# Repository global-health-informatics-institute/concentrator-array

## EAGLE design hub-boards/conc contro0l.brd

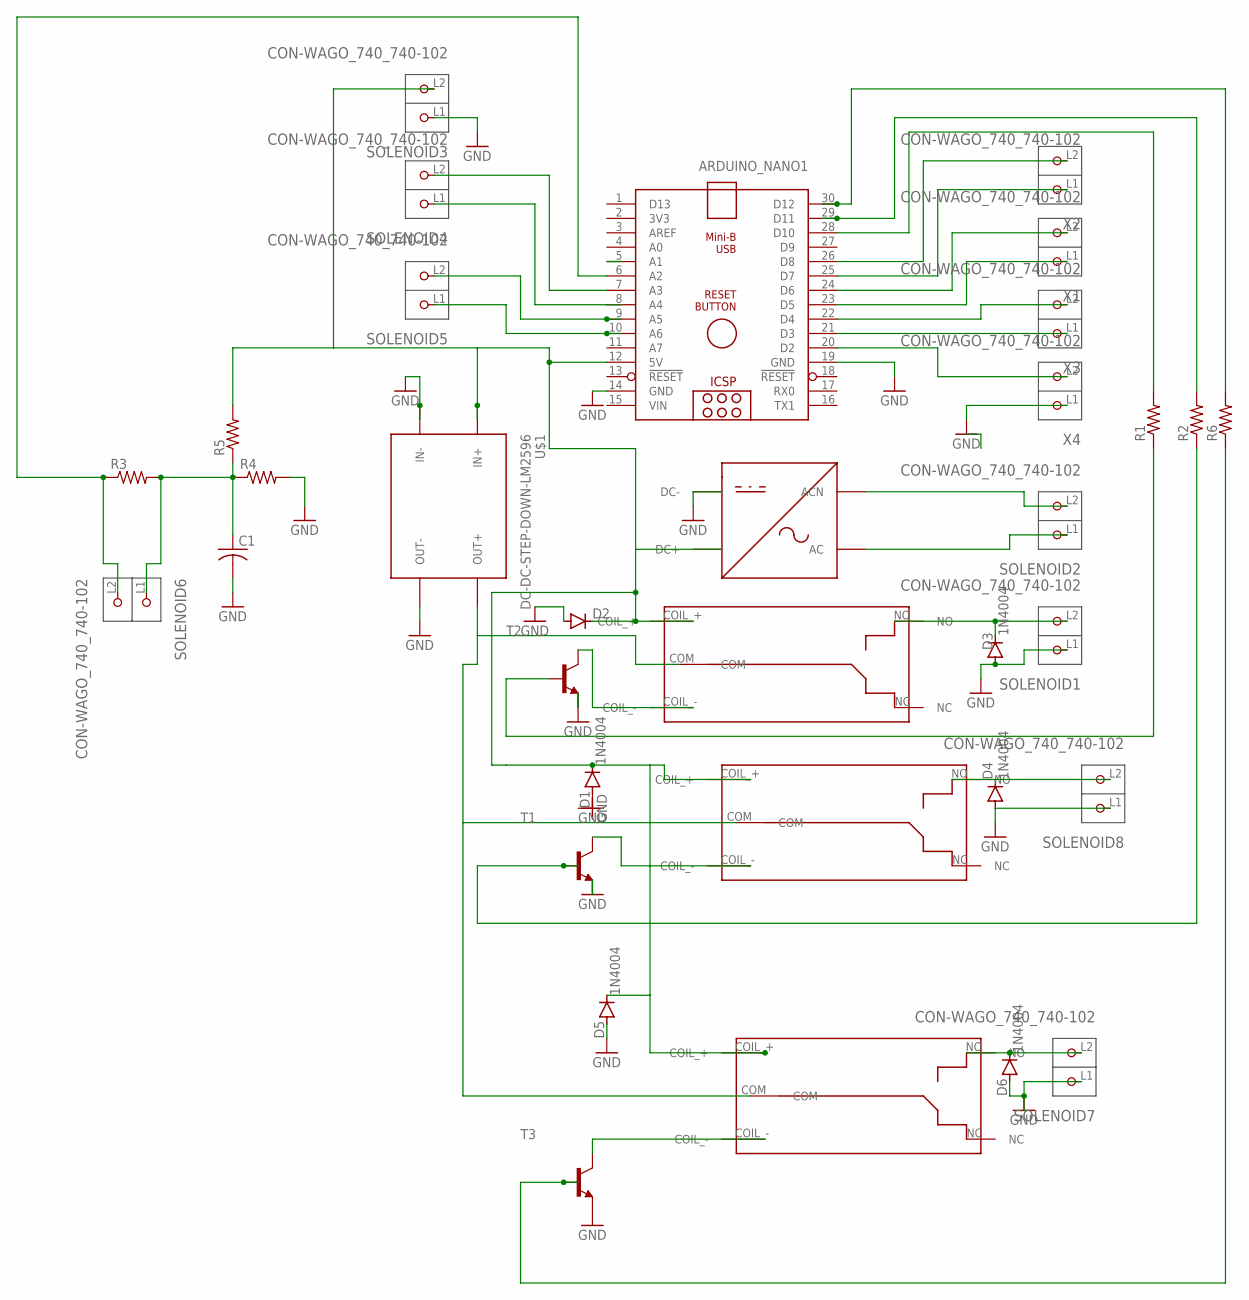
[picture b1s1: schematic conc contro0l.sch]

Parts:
ACDC: RPD10W1S; 2343
ARDUINO_NANO1: ARDUINONANOV30-GHIT_ARDUINO_NANO
C1: C-US025-024X044; C025-024X044
D1, D2, D3, D4, D5, D6: 1N4004; DO41-10
R1, R2, R6: R-US_0411/15; 0411/15
R3, R4, R5: R-US_0309/10; 0309/10
SOLENOID1, SOLENOID2, SOLENOID3, SOLENOID4, SOLENOID5, SOLENOID6, SOLENOID7, SOLENOID8: CON-WAGO_740_740-102; CON-WAGO_740_P-740-102
T1, T2, T3: 2N2222-NPN-TO92-EBC; TO92-EBC
U$1: DC-DC-STEP-DOWN-LM2596
U$2, U$3, U$4: RELAY_JQC-3F(T73)A; JQC-3F(T73)
X1, X2, X3, X4: CON-WAGO_740_740-102; CON-WAGO_740_P-740-102

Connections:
GND: ACDC.DC-, ARDUINO_NANO1.14 (GND), ARDUINO_NANO1.19 (GND), C1.2, D1.A, D2.A, D3.A, D4.A, D5.A, D6.A, R4.2, SOLENOID1.L1 (P1), SOLENOID3.L1 (P1), SOLENOID7.L1 (P1), SOLENOID8.L1 (P1), T1.E, T2.E, T3.E, U$1.IN-, U$1.OUT-, X4.L1 (P1)
unnamed: ARDUINO_NANO1.7 (A3), SOLENOID4.L2 (P2)
unnamed: ARDUINO_NANO1.20 (D2), X4.L2 (P2)
unnamed: ARDUINO_NANO1.21 (D3), X3.L1 (P1)
unnamed: ARDUINO_NANO1.22 (D4), X3.L2 (P2)
unnamed: ARDUINO_NANO1.23 (D5), X1.L1 (P1)
unnamed: ARDUINO_NANO1.24 (D6), X1.L2 (P2)
unnamed: ARDUINO_NANO1.28 (D10), R1.2
unnamed: ARDUINO_NANO1.26 (D8), X2.L2 (P2)
unnamed: ARDUINO_NANO1.9 (A5), SOLENOID5.L2 (P2)
unnamed: ACDC.DC+, ARDUINO_NANO1.12 (5V), D1.C, D2.C, D5.C, R5.2, SOLENOID3.L2 (P2), U$1.IN+, U$2.COIL_+, U$3.COIL_+, U$4.COIL_+
unnamed: ACDC.ACN, SOLENOID2.L2 (P2)
unnamed: ARDUINO_NANO1.10 (A6), SOLENOID5.L1 (P1)
unnamed: D3.C, SOLENOID1.L2 (P2), U$2.NO
unnamed: D4.C, SOLENOID8.L2 (P2), U$3.NO
unnamed: T2.C, U$2.COIL_-
unnamed: R2.1, T1.B
unnamed: ARDUINO_NANO1.25 (D7), X2.L1 (P1)
unnamed: ACDC.AC, SOLENOID2.L1 (P1)
unnamed: C1.1, R3.2, R4.1, R5.1, SOLENOID6.L1 (P1)
unnamed: R1.1, T2.B
unnamed: T1.C, U$3.COIL_-
unnamed: ARDUINO_NANO1.8 (A4), SOLENOID4.L1 (P1)
unnamed: R6.1, T3.B
unnamed: ARDUINO_NANO1.6 (A2), R3.1, SOLENOID6.L2 (P2)
unnamed: U$1.OUT+, U$2.COM, U$3.COM, U$4.COM
unnamed: ARDUINO_NANO1.29 (D11), R2.2
unnamed: ARDUINO_NANO1.30 (D12), R6.2
unnamed: T3.C, U$4.COIL_-
unnamed: D6.C, SOLENOID7.L2 (P2), U$4.NO
VIN: ARDUINO_NANO1.15 (VIN)

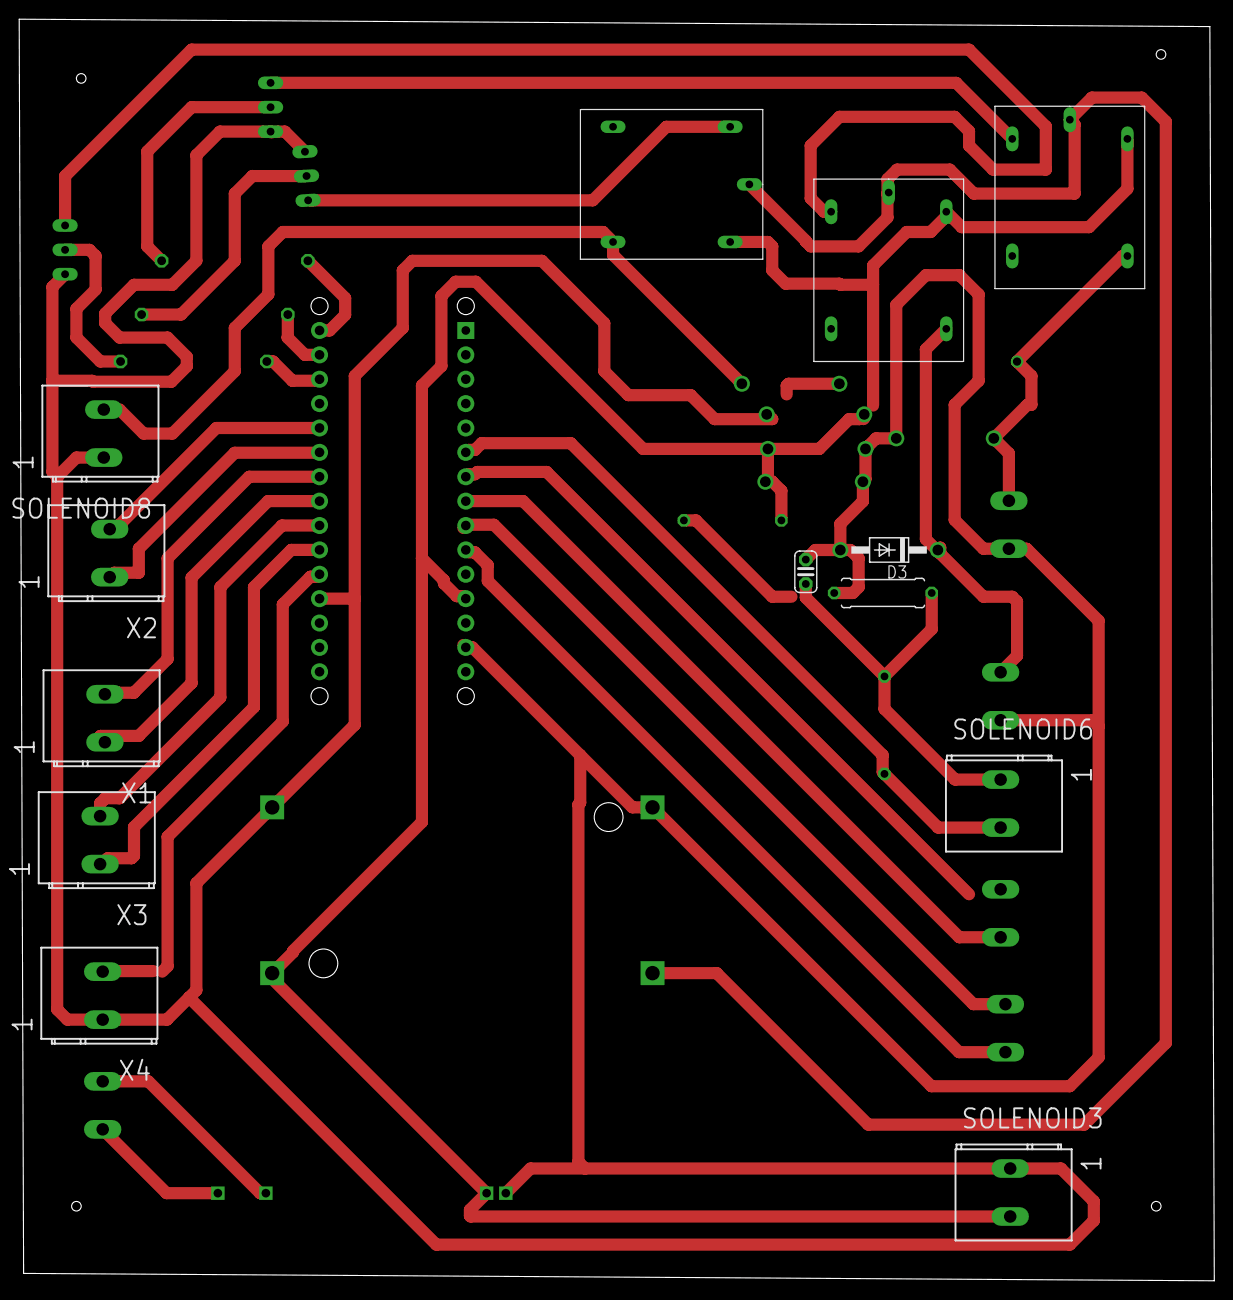
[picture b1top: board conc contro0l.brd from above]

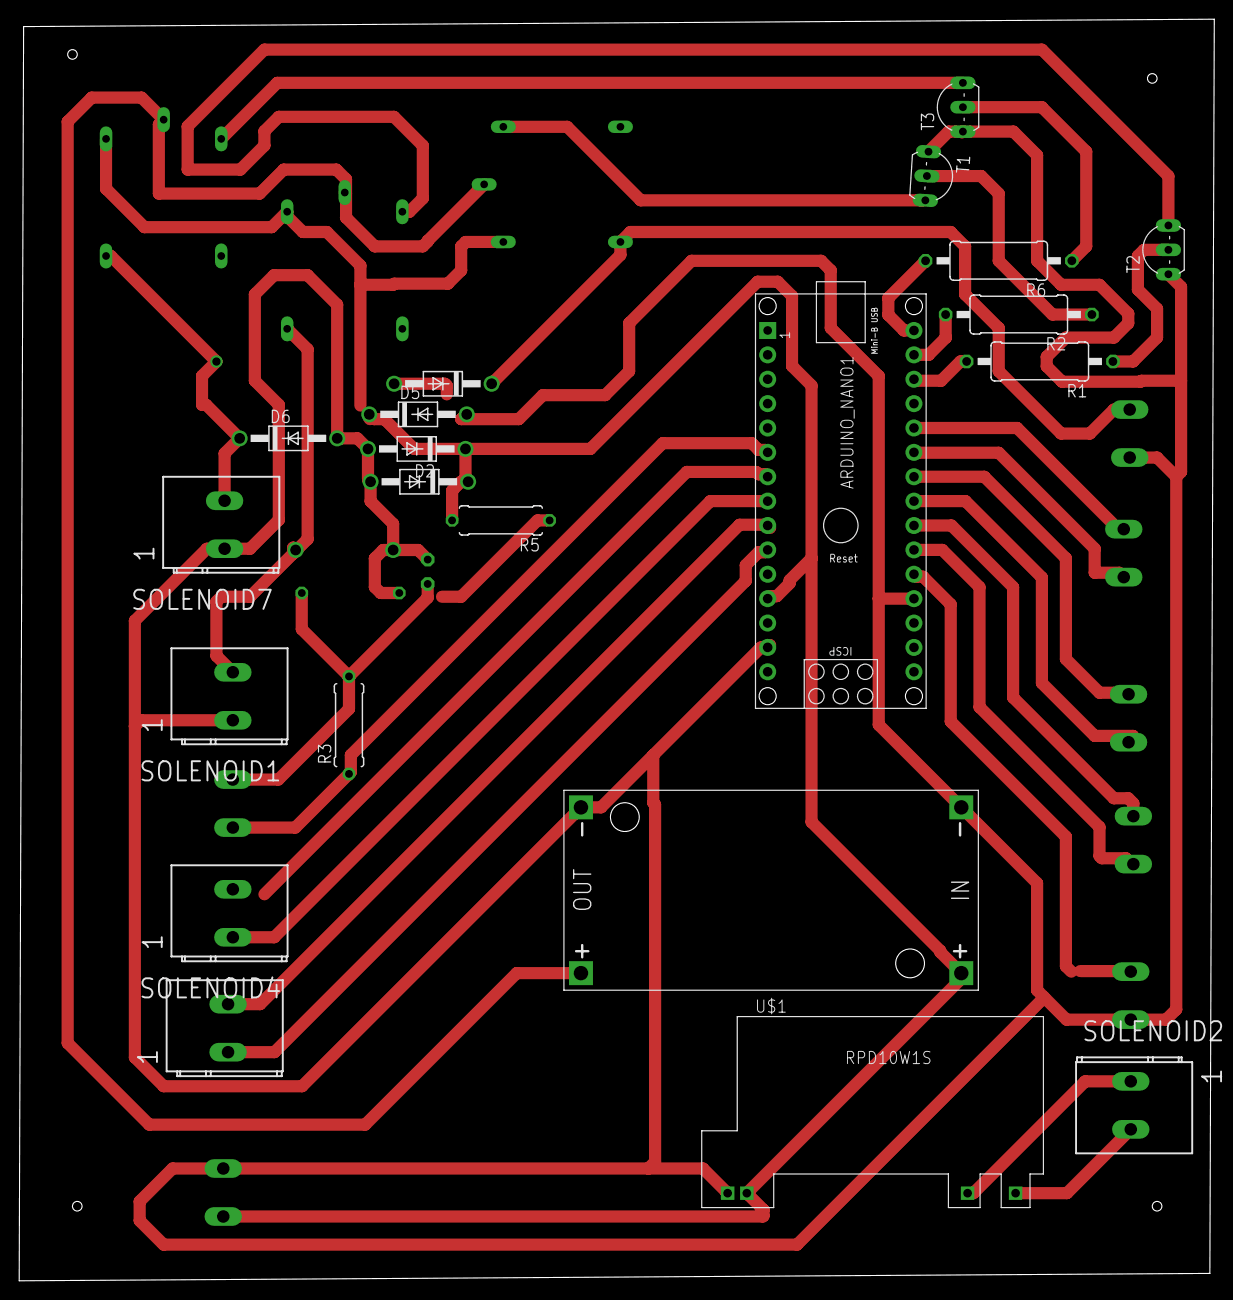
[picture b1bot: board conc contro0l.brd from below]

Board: 2 copper layers, 124.5 x 131.4 mm, 34 parts (21 on the bottom side), 30 nets.

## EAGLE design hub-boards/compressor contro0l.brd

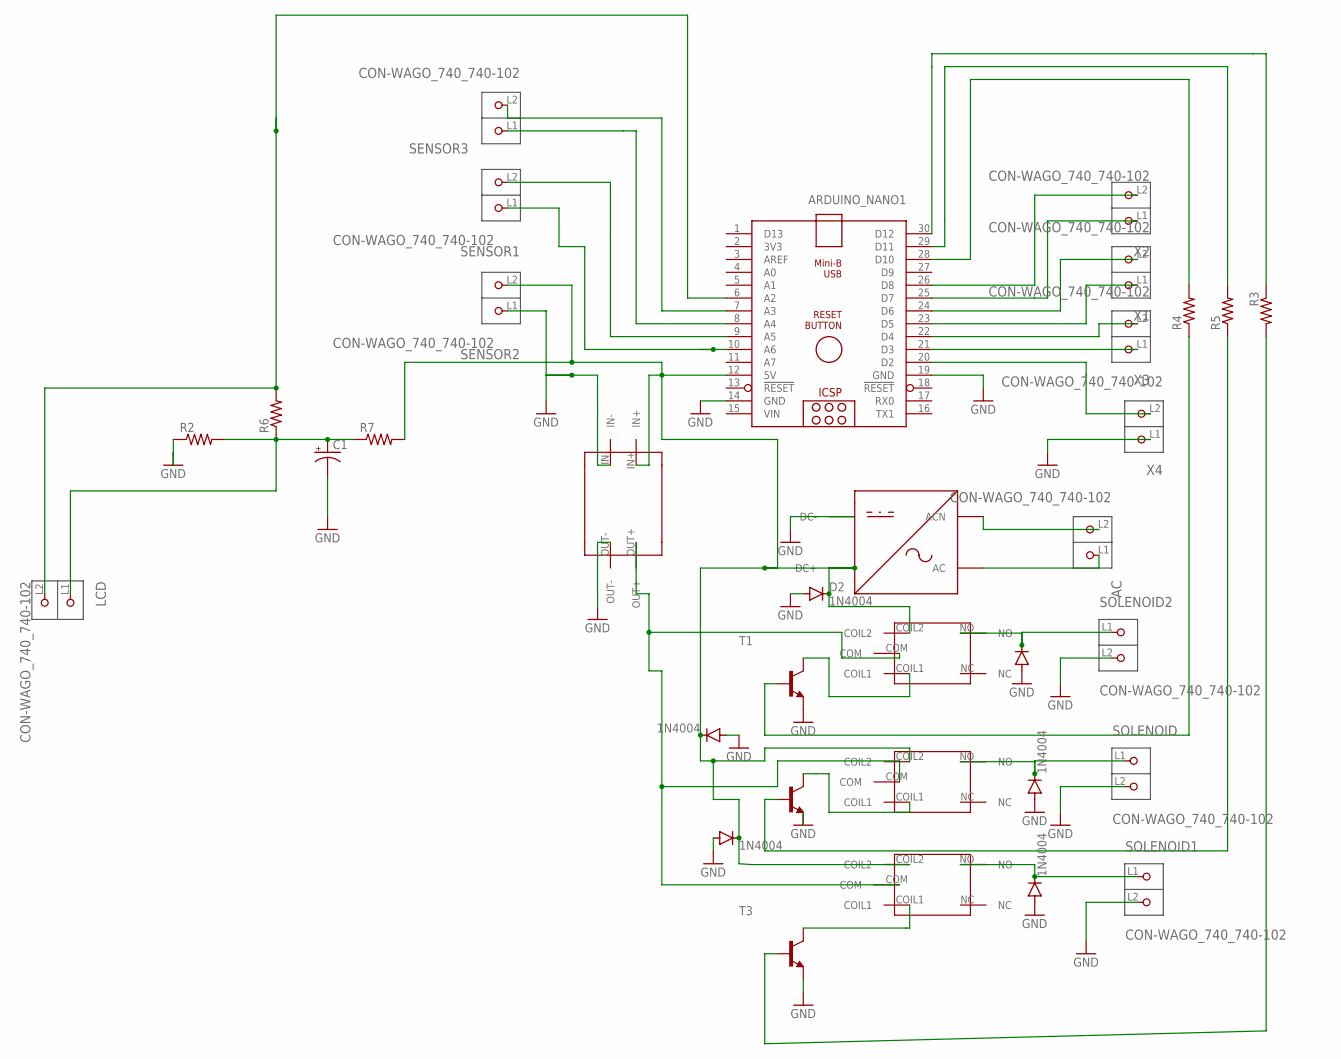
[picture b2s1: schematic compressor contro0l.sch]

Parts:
AC: CON-WAGO_740_740-102; CON-WAGO_740_P-740-102
ACDC: RPD10W1S; 2343
ARDUINO_NANO1: ARDUINONANOV30-GHIT_ARDUINO_NANO
C1: CPOL-USE3.5-8; E3,5-8
D2, D3, D4, D5, D6, D7: 1N4004; DO41-10
LCD: CON-WAGO_740_740-102; CON-WAGO_740_P-740-102
R2, R6, R7: R-US_0207/10; 0207/10
R3, R4, R5: R-US_0613/15; P0613/15
SENSOR1, SENSOR2, SENSOR3: CON-WAGO_740_740-102; CON-WAGO_740_P-740-102
SOLENOID, SOLENOID1, SOLENOID2: CON-WAGO_740_740-102; CON-WAGO_740_P-740-102
T1, T2, T3: 2N2222-NPN-TO92-EBC; TO92-EBC
U$2: DC-DCBUCK
U$3, U$4, U$5: MRELAY2MRELAY2; MRELAY
X1, X2, X3, X4: CON-WAGO_740_740-102; CON-WAGO_740_P-740-102

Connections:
GND: ACDC.DC-, ARDUINO_NANO1.14 (GND), ARDUINO_NANO1.19 (GND), C1.-, D2.A, D3.A, D4.A, D5.A, D6.A, D7.A, R2.1, SENSOR2.L1 (P1), SOLENOID.L2 (P2), SOLENOID1.L2 (P2), SOLENOID2.L2 (P2), T1.E, T2.E, T3.E, U$2.IN-, U$2.OUT-, X4.L1 (P1)
unnamed: ARDUINO_NANO1.9 (A5), SENSOR1.L2 (P2)
unnamed: ARDUINO_NANO1.20 (D2), X4.L2 (P2)
unnamed: ARDUINO_NANO1.21 (D3), X3.L1 (P1)
unnamed: ARDUINO_NANO1.22 (D4), X3.L2 (P2)
unnamed: ARDUINO_NANO1.23 (D5), X1.L1 (P1)
unnamed: ARDUINO_NANO1.24 (D6), X1.L2 (P2)
unnamed: ARDUINO_NANO1.30 (D12), R3.1
unnamed: ARDUINO_NANO1.25 (D7), X2.L1 (P1)
unnamed: ACDC.DC+, ARDUINO_NANO1.12 (5V), D2.C, D4.C, D5.C, R7.2, SENSOR2.L2 (P2), U$2.IN+, U$3.COIL2, U$4.COIL2, U$5.COIL2
unnamed: ARDUINO_NANO1.10 (A6), SENSOR1.L1 (P1)
unnamed: AC.L2 (P2), ACDC.ACN
unnamed: ARDUINO_NANO1.8 (A4), SENSOR3.L1 (P1)
unnamed: AC.L1 (P1), ACDC.AC
unnamed: ARDUINO_NANO1.28 (D10), R4.2
unnamed: R4.1, T1.B
unnamed: ARDUINO_NANO1.29 (D11), R5.2
unnamed: ARDUINO_NANO1.26 (D8), X2.L2 (P2)
unnamed: U$2.OUT+, U$3.COM, U$4.COM, U$5.COM
unnamed: ARDUINO_NANO1.7 (A3), SENSOR3.L2 (P2)
unnamed: R3.2, T3.B
unnamed: R5.1, T2.B
unnamed: T2.C, U$3.COIL1
unnamed: T1.C, U$4.COIL1
unnamed: T3.C, U$5.COIL1
unnamed: D7.C, SOLENOID1.L1 (P1), U$5.NO
unnamed: D6.C, SOLENOID2.L1 (P1), U$4.NO
unnamed: D3.C, SOLENOID.L1 (P1), U$3.NO
unnamed: ARDUINO_NANO1.6 (A2), LCD.L2 (P2), R6.2
unnamed: C1.+, LCD.L1 (P1), R2.2, R6.1, R7.1
VIN: ARDUINO_NANO1.15 (VIN)

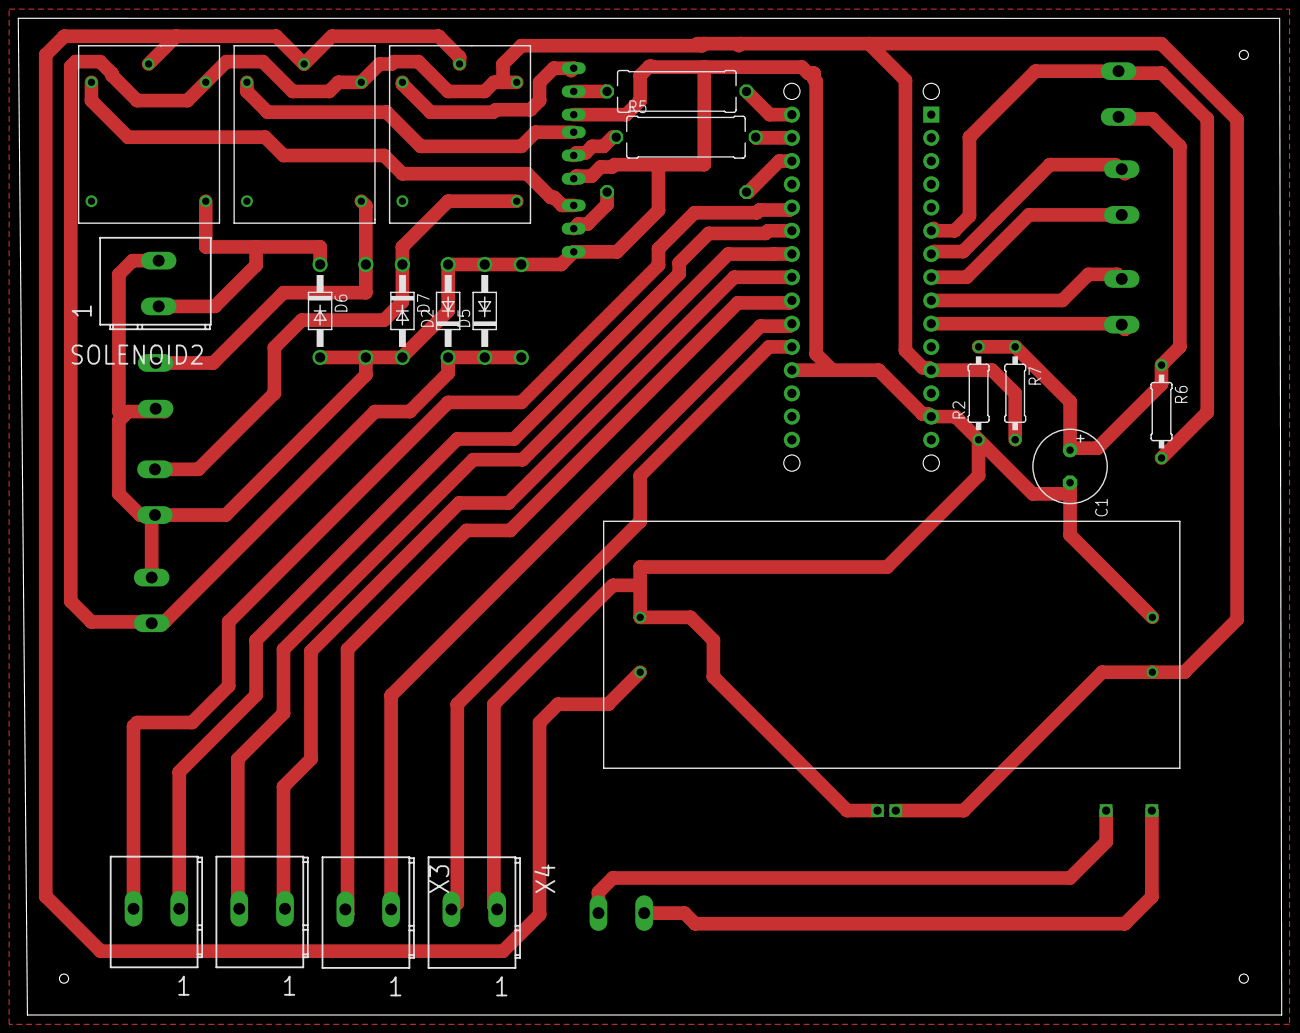
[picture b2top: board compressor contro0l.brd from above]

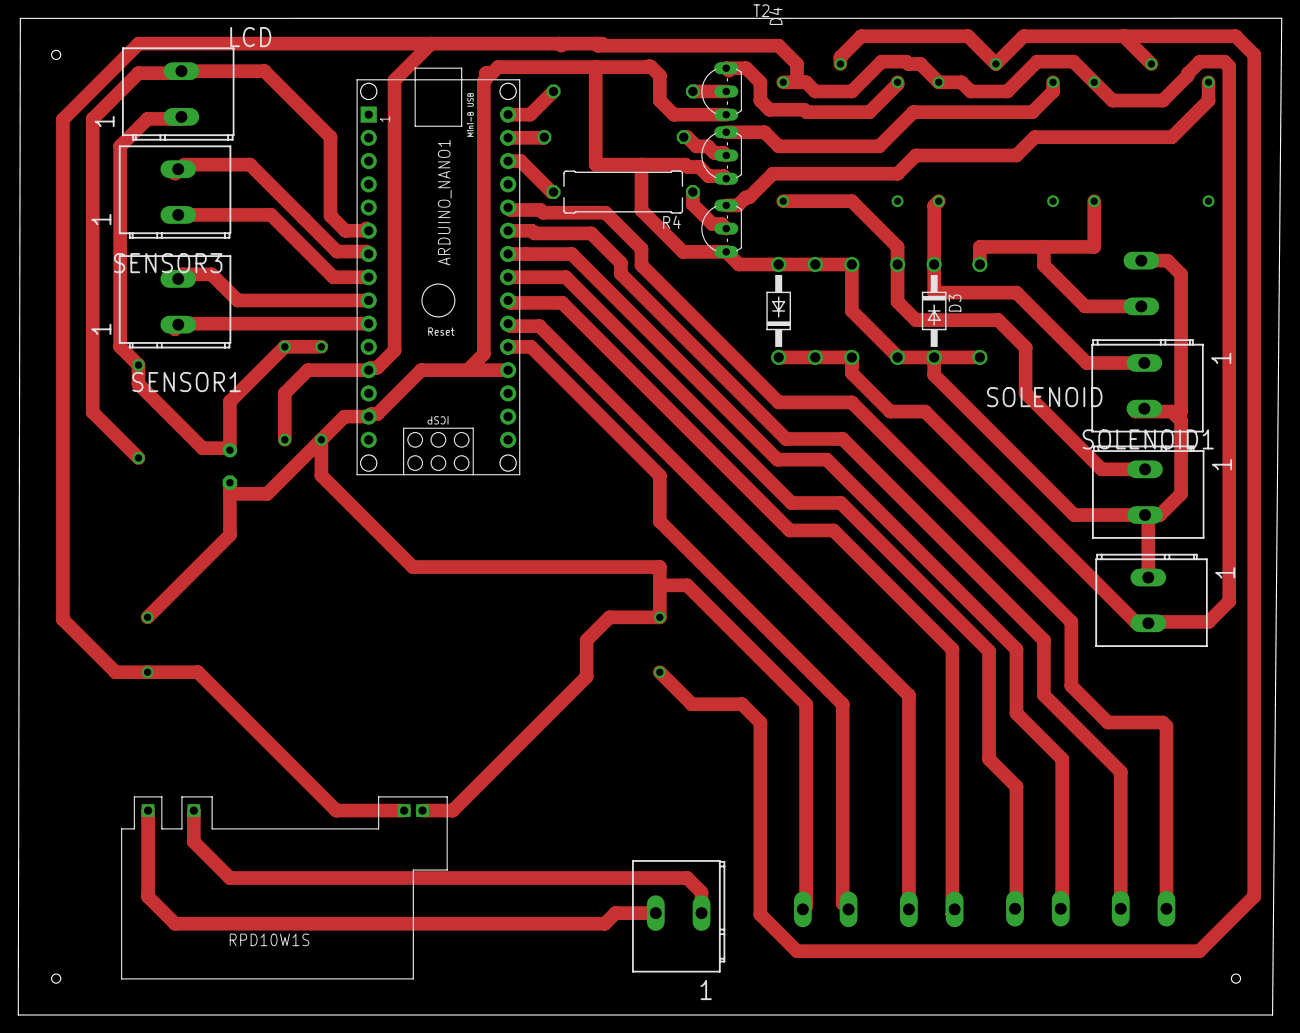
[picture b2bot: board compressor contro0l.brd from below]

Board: 2 copper layers, 138.1 x 109.0 mm, 34 parts (15 on the bottom side), 30 nets.

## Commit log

2022-02-16 update1
2022-03-02 Third update
2022-03-04 fourth update
2022-03-04 fifth update
2022-03-24 sixth update
2022-03-24 board
2022-03-30 board2
2023-02-06 changed the max pressure and min pressure
2023-02-09 Add files via upload
    changed max and min pressure update number 2
2023-02-13 Add files via upload
    changed max and min pressure in the low pressure tank and purging when compressol_off is called
2023-02-21 Add files via upload
    1st update,new code
2023-02-22 New code,2nd update
    added High pressure > 20 and High pressure <50
2023-03-09 Array finite state 1
    this code has the first four states,;
2023-03-09 Array finite state 2
    This code has all the 7 states
2023-03-15 Array finite state 3
    This code has all the 7 states with a purging delay of 1 second
2023-03-21 Array finite state 3
    This code has comments

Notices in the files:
parts and their libraries:
GHIdiy-modules: Released under the Creative Commons Attribution 4.0 International License: http://creativecommons.org/licenses/by/4.0
